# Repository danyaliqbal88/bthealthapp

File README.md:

# HealthApp
First app
"# bthealthapp" 
Ionic app for Riko chi.
The Riko Chi is an ultra low power, ultra light, ultra small wearable smartwatch. It monitors the ECG and the PPG 
signals to calculate your blood pressure non-invasively.The smartwatch must be calibrated
1. The physical address of the HC-05 Bluetooth module is hardcoded. Change it in index.js file according to your 
Hardware module.

Warning:
Despite the chic 3D printable design, the Riko Chi is a biomedical device and should be treated as a medical 
instrument for all intents and purposes. The Riko Chi must be re- calibrated for each individual patient.
The calibration process requires the patient to undergo a cardiac exercise test while wearing the Riko Chi in 
calibration mode and simultaneous reading obtained from an automatic cuff based blood pressure machine at 
regular intervals. Once the device has been calibrated, it can estimate the systolic Blood pressure of that individual 
with a mean error of +- 10.6 mmHG.
Beware:The risk for electric shock and accidental injury or loss of life exists.

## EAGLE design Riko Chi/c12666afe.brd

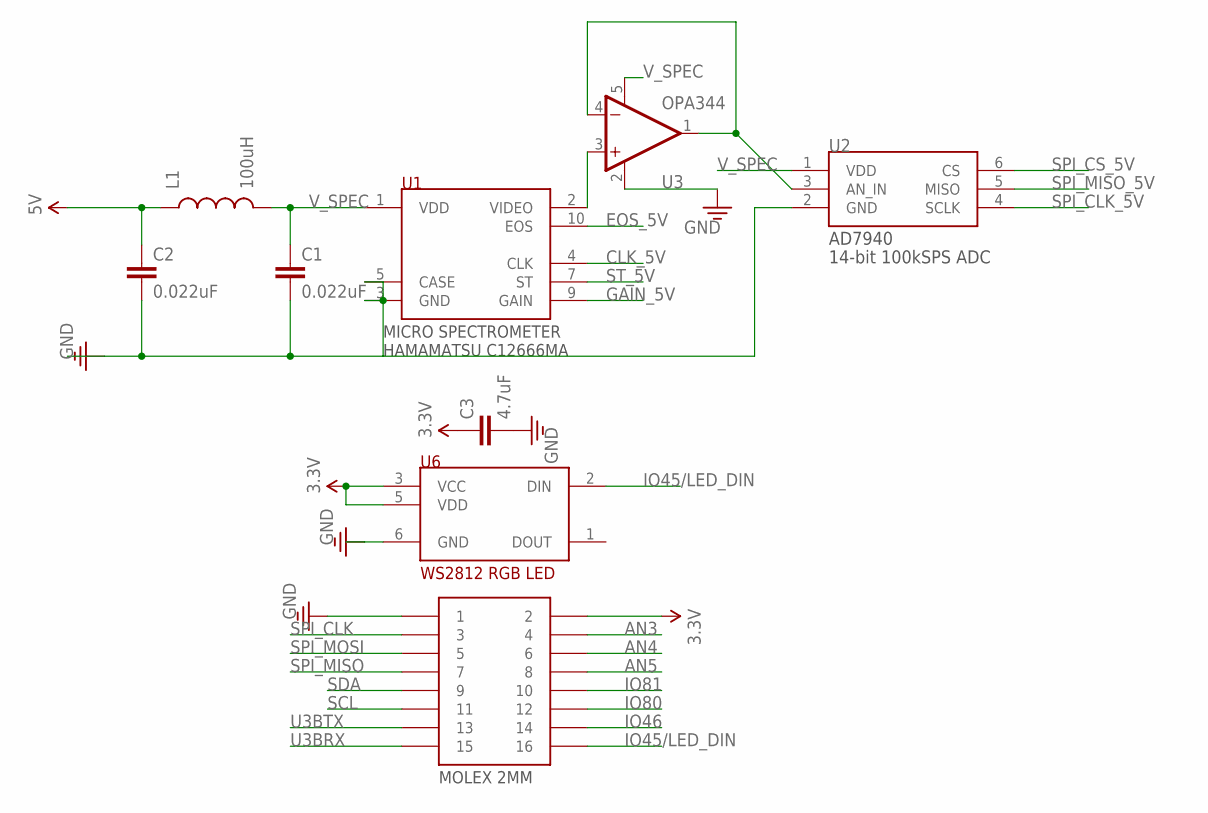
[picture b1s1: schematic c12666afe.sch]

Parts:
2MMCONNECTOR: CON-MOLEX-2MMMALE; MOLEX-0877591650
C1, C2: 0.022uF; 0603
C3: 4.7uF; 0603
L1: 100uH; 0805
U1: MICROSPEC-C12666MA; C12666MA
U2: AD7940; SOT-23-6L
U3: OPA344; SOT23-5
U6: WS2812_NEOPIXEL; WS2812

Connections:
3.3V: 2MMCONNECTOR.2, C3.1, U6.3 (VCC), U6.5 (VDD)
5V: C2.1, L1.1
AN3: 2MMCONNECTOR.4
AN4: 2MMCONNECTOR.6
AN5: 2MMCONNECTOR.8
CLK_5V: U1.4 (CLK)
EOS_5V: U1.10 (EOS)
GAIN_5V: U1.9 (GAIN)
GND: 2MMCONNECTOR.1, C1.2, C2.2, C3.2, U1.3 (GND), U1.5 (CASE), U2.2 (GND), U3.2 (V-), U6.6 (GND)
IO45/LED_DIN: 2MMCONNECTOR.16, U6.2 (DIN)
IO46: 2MMCONNECTOR.14
IO80: 2MMCONNECTOR.12
IO81: 2MMCONNECTOR.10
unnamed: U2.3 (AN_IN), U3.1 (OUT), U3.4 (-IN)
unnamed: U1.2 (VIDEO), U3.3 (+IN)
SCL: 2MMCONNECTOR.11
SDA: 2MMCONNECTOR.9
SPI_CLK: 2MMCONNECTOR.3
SPI_CLK_5V: U2.4 (SCLK)
SPI_CS_5V: U2.6 (CS)
SPI_MISO: 2MMCONNECTOR.7
SPI_MISO_5V: U2.5 (MISO)
SPI_MOSI: 2MMCONNECTOR.5
ST_5V: U1.7 (ST)
U3BRX: 2MMCONNECTOR.15
U3BTX: 2MMCONNECTOR.13
V_SPEC: C1.1, L1.2, U1.1 (VDD), U2.1 (VDD), U3.5 (V+)

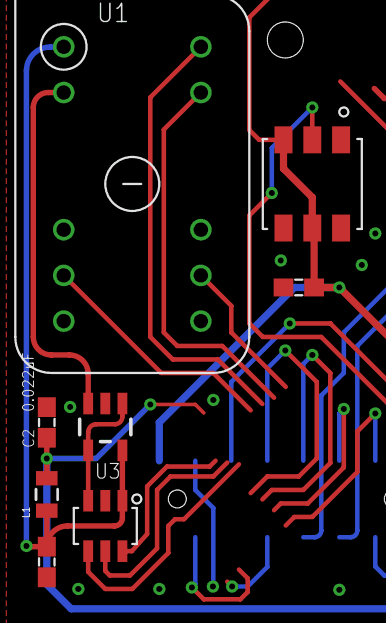
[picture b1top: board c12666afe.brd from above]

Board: 2 copper layers, 9 parts (1 on the bottom side), 7 nets.

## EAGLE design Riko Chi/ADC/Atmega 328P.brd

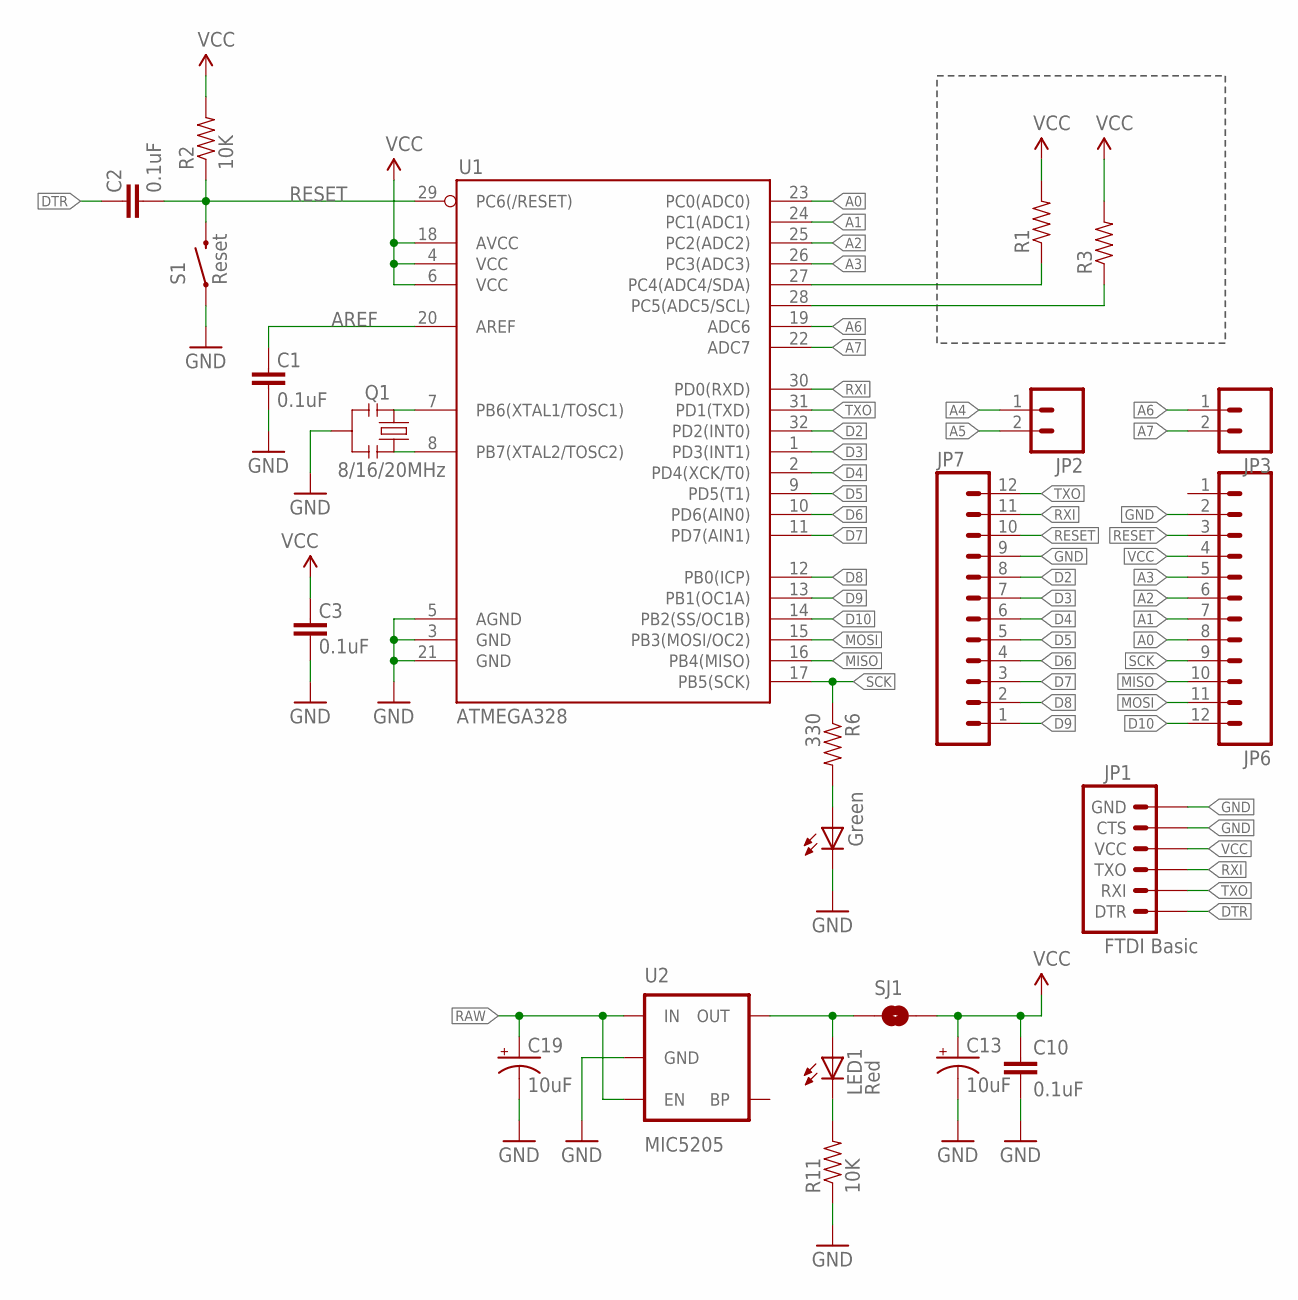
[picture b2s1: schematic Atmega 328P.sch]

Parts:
C1, C2, C3, C10: 0.1uF; 0603-CAP
C13, C19: 10uF; EIA3216
D3: Green; 0603-LED-ALT1
JP1: FTDI Basic; 1X06
JP2, JP3: M02PTH; 1X02
JP6, JP7: M12PTH; 1X12
LED1: Red; 0603-LED-ALT1
Q1: 8/16/20MHz; RESONATOR-SMD-1:1
R1, R3: RESISTOR0603-RES; 0603-RES
R2, R11: 10K; 0603-RES
R6: 330; 0603-RES
S1: Reset; TACTILE-SWITCH-SMD-ALT01
SJ1: SOLDERJUMPERNC; SJ_2S
U1: ATMEGA328; TQFP32-08
U2: MIC5205; SOT23-5

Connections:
A0: JP6.8, U1.23 (PC0(ADC0))
A1: JP6.7, U1.24 (PC1(ADC1))
A2: JP6.6, U1.25 (PC2(ADC2))
A3: JP6.5, U1.26 (PC3(ADC3))
A4: JP2.1, R1.1, U1.27 (PC4(ADC4/SDA))
A5: JP2.2, R3.1, U1.28 (PC5(ADC5/SCL))
A6: JP3.1, U1.19 (ADC6)
A7: JP3.2, U1.22 (ADC7)
AREF: C1.2, U1.20 (AREF)
D2: JP7.8, U1.32 (PD2(INT0))
D3: JP7.7, U1.1 (PD3(INT1))
D4: JP7.6, U1.2 (PD4(XCK/T0))
D5: JP7.5, U1.9 (PD5(T1))
D6: JP7.4, U1.10 (PD6(AIN0))
D7: JP7.3, U1.11 (PD7(AIN1))
D8: JP7.2, U1.12 (PB0(ICP))
D9: JP7.1, U1.13 (PB1(OC1A))
D10: JP6.12, U1.14 (PB2(SS/OC1B))
DTR: C2.2, JP1.1 (DTR)
GND: C1.1, C3.1, C10.2, C13.C (-), C19.C (-), D3.C, JP1.5 (CTS), JP1.6 (GND), JP6.2, JP7.9, Q1.2, R11.1, S1.1, S1.2 (1), U1.3 (GND), U1.5 (AGND), U1.21 (GND), U2.2 (GND)
MISO: JP6.10, U1.16 (PB4(MISO))
MOSI: JP6.11, U1.15 (PB3(MOSI/OC2))
unnamed: Q1.3, U1.8 (PB7(XTAL2/TOSC2))
unnamed: Q1.1, U1.7 (PB6(XTAL1/TOSC1))
unnamed: LED1.A, SJ1.1, U2.5 (OUT)
unnamed: LED1.C, R11.2
unnamed: D3.A, R6.2
RAW: C19.A (+), U2.1 (IN), U2.3 (EN)
RESET: C2.1, JP6.3, JP7.10, R2.1, S1.3 (2), S1.4 (2), U1.29 (PC6(/RESET))
RXI: JP1.3 (TXO), JP7.11, U1.30 (PD0(RXD))
SCK: JP6.9, R6.1, U1.17 (PB5(SCK))
TXO: JP1.2 (RXI), JP7.12, U1.31 (PD1(TXD))
VCC: C3.2, C10.1, C13.A (+), JP1.4 (VCC), JP6.4, R1.2, R2.2, R3.2, SJ1.2, U1.4 (VCC), U1.6 (VCC), U1.18 (AVCC)

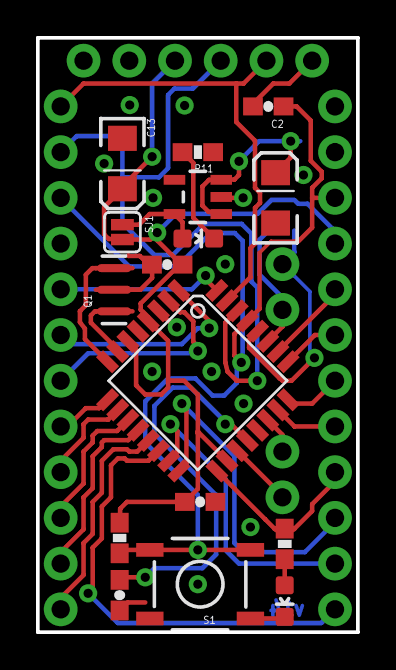
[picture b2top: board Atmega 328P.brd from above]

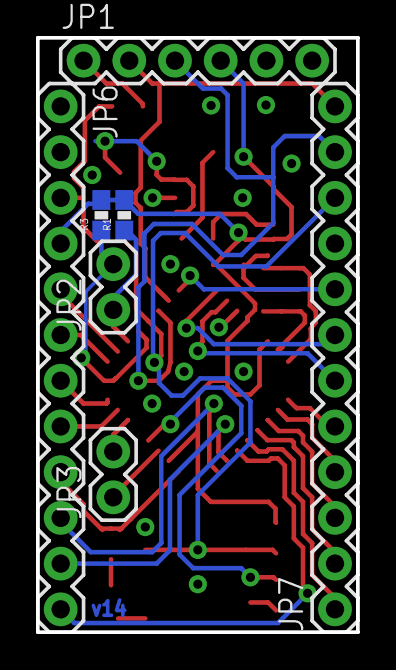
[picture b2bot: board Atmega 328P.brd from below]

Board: 2 copper layers, 17.8 x 33.0 mm, 23 parts (7 on the bottom side), 33 nets.

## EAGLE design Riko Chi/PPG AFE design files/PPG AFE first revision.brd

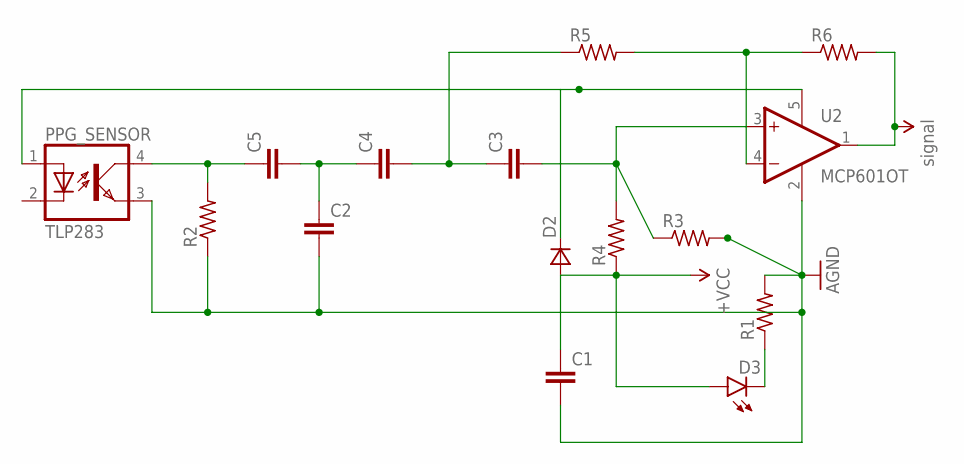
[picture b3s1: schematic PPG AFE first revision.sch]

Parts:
C1, C2, C3, C4, C5: CC0201; C0201
D2: DSOD323; SOD323
D3: LED-FKIT-1206; FKIT-LED-1206
PPG_SENSOR: TLP283; MINI-FLAT-4
R1, R2, R3, R4, R5, R6: R-US_R0603; R0603
U2: MCP601OT; SOT23-5

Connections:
AGND: C1.2, C2.2, PPG_SENSOR.3 (EMIT), R1.2, R2.1, R3.2, U2.2 (V-)
unnamed: C3.2, R3.1, R4.2, U2.3 (+IN)
unnamed: R5.2, R6.1, U2.4 (-IN)
unnamed: D2.1 (C), PPG_SENSOR.1 (A), U2.5 (V+)
unnamed: C3.1, C4.2, R5.1
unnamed: C2.1, C4.1, C5.2
unnamed: C5.1, PPG_SENSOR.4 (COL), R2.2
unnamed: D3.C, R1.1
VCC: C1.1, D2.2 (A), D3.A, R4.1
VCC_1: R6.2, U2.1 (OUT)

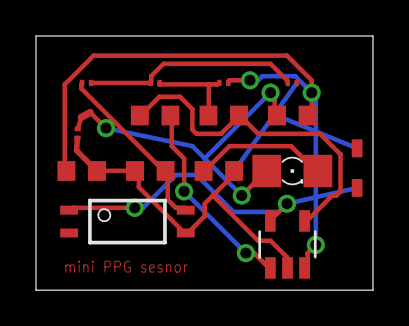
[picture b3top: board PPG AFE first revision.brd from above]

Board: 2 copper layers, 18.7 x 14.1 mm, 15 parts (0 on the bottom side), 10 nets.

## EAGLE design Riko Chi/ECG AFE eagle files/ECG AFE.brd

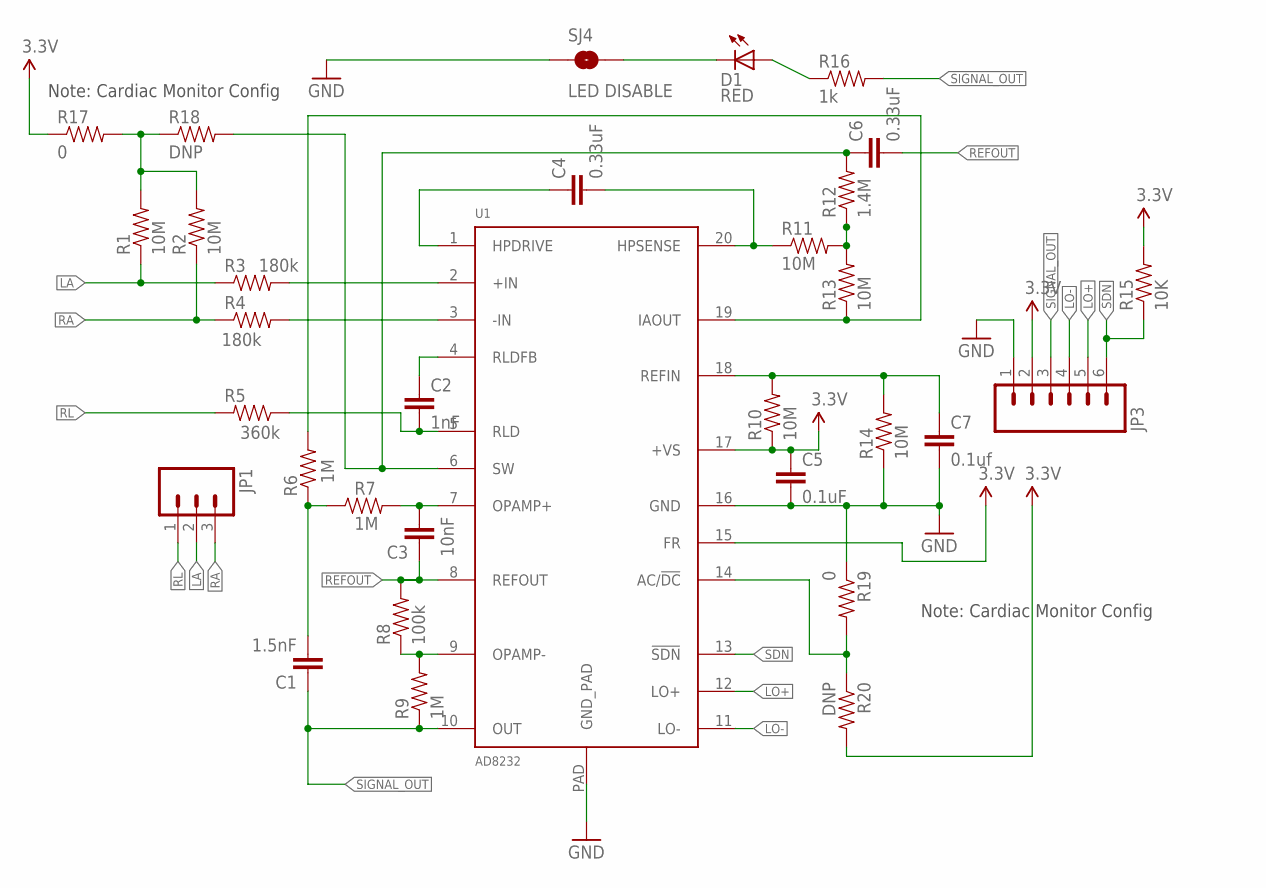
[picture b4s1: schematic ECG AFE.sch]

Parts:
C1: 1.5nF; 0603-CAP
C2: 1nF; 0603-CAP
C3: 10nF; 0603-CAP
C4, C6: 0.33uF; 0805
C5: 0.1uF; 0603-CAP
C7: 0.1uf; 0603-CAP
D1: RED; LED-0603
JP1: M03PTH; 1X03
JP3: M06SIP; 1X06
R1, R2, R10, R11, R13, R14: 10M; 0603-RES
R3, R4: 180k; 0603-RES
R5: 360k; 0603-RES
R6, R7, R9: 1M; 0603-RES
R8: 100k; 0603-RES
R12: 1.4M; 0603-RES
R15: 10K; 0603-RES
R16: 1k; 0603-RES
R17, R19: 0; 0603
R18, R20: DNP; 0603
SJ4: LED DISABLE; SJ_2S-TRACE
U1: AD8232; LFCSP_20

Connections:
3.3V: C5.1, JP3.2, R10.1, R15.2, R17.1, R20.2, U1.15 (FR), U1.17 (+VS)
GND: C5.2, C7.2, JP3.1, R14.1, R19.1, SJ4.1, U1.16 (GND), U1.PAD (GND_PAD)
LA: JP1.2, R1.1, R3.1
LO+: JP3.5, U1.12 (LO+)
LO-: JP3.4, U1.11 (LO-)
unnamed: R3.2, U1.2 (+IN)
unnamed: R4.2, U1.3 (-IN)
unnamed: C3.2, R7.2, U1.7 (OPAMP+)
unnamed: C4.2, R11.1, U1.20 (HPSENSE)
unnamed: C7.1, R10.2, R14.2, U1.18 (REFIN)
unnamed: D1.A, R16.1
unnamed: R8.1, R9.2, U1.9 (OPAMP-)
unnamed: R6.2, R13.1, U1.19 (IAOUT)
unnamed: C1.2, R6.1, R7.1
unnamed: D1.C, SJ4.2
unnamed: R19.2, R20.1, U1.14 (AC/!DC)
unnamed: C4.1, U1.1 (HPDRIVE)
unnamed: R11.2, R12.1, R13.2
unnamed: C6.1, R12.2, R18.2, U1.6 (SW)
unnamed: C2.1, U1.4 (RLDFB)
unnamed: C2.2, R5.1, U1.5 (RLD)
unnamed: R1.2, R2.2, R17.2, R18.1
RA: JP1.3, R2.1, R4.1
REFOUT: C3.1, C6.2, R8.2, U1.8 (REFOUT)
RL: JP1.1, R5.2
SDN: JP3.6, R15.1, U1.13 (!SDN)
SIGNAL_OUT: C1.1, JP3.3, R9.1, R16.2, U1.10 (OUT)

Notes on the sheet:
Note: Cardiac Monitor Config

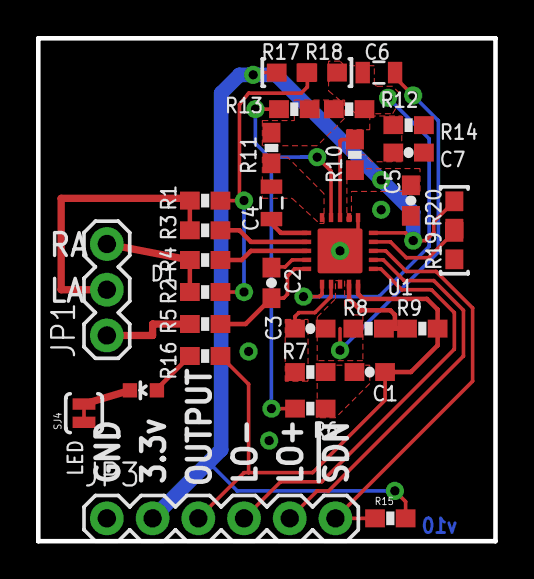
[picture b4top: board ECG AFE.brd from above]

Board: 2 copper layers, 25.4 x 27.9 mm, 32 parts (0 on the bottom side), 27 nets.

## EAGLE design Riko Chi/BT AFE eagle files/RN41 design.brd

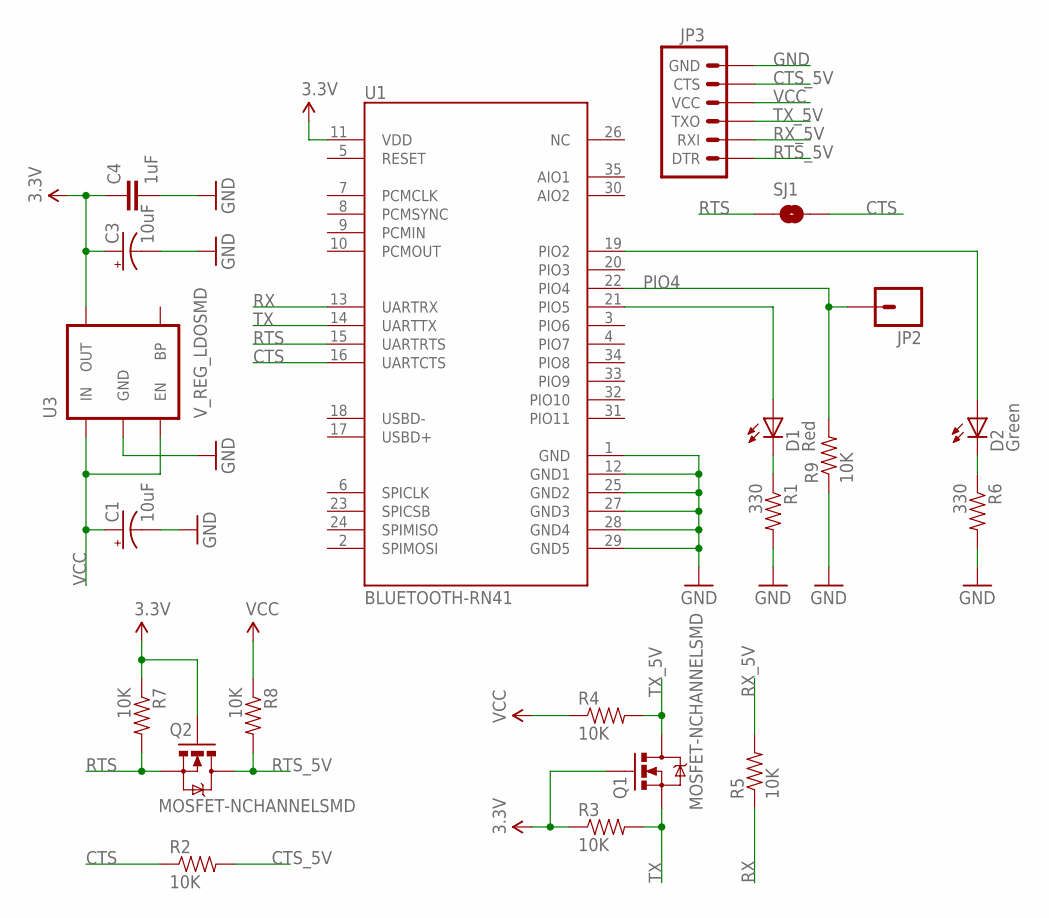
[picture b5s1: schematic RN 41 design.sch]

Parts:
C1, C3: 10uF; EIA3216
C4: 1uF; 0402-CAP
D1: Red; LED-0603
D2: Green; LED-0603
JP2: M01SMDNS; 1X01NS
JP3: ARDUINO_SERIAL_PROGRAMPTH; 1X06
Q1, Q2: MOSFET-NCHANNELSMD; SOT23-3
R1, R6: 330; 0402-RES
R2, R3, R4, R5, R7, R8, R9: 10K; 0402-RES
SJ1: SOLDERJUMPERNO; SJ_2S-NO
U1: BLUETOOTH-RN41; RN41
U3: V_REG_LDOSMD; SOT23-5

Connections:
3.3V: C3.A (+), C4.1, Q1.1 (G), Q2.1 (G), R3.1, R7.1, U1.11 (VDD), U3.5 (OUT)
CTS: R2.1, SJ1.2, U1.16 (UARTCTS)
CTS_5V: JP3.5 (CTS), R2.2
D1: D1.C, R1.1
D2: D2.C, R6.1
GND: C1.C (-), C3.C (-), C4.2, JP3.6 (GND), R1.2, R6.2, R9.1, U1.1 (GND), U1.12 (GND1), U1.25 (GND2), U1.27 (GND3), U1.28 (GND4), U1.29 (GND5), U3.2 (GND)
unnamed: D1.A, U1.21 (PIO5)
unnamed: D2.A, U1.19 (PIO2)
PIO4: JP2.1, R9.2, U1.22 (PIO4)
RTS: Q2.2 (S), R7.2, SJ1.1, U1.15 (UARTRTS)
RTS_5V: JP3.1 (DTR), Q2.3 (D), R8.2
RX: R5.1, U1.13 (UARTRX)
RX_5V: JP3.2 (RXI), R5.2
TX: Q1.2 (S), R3.2, U1.14 (UARTTX)
TX_5V: JP3.3 (TXO), Q1.3 (D), R4.2
VCC: C1.A (+), JP3.4 (VCC), R4.1, R8.1, U3.1 (IN), U3.3 (EN)

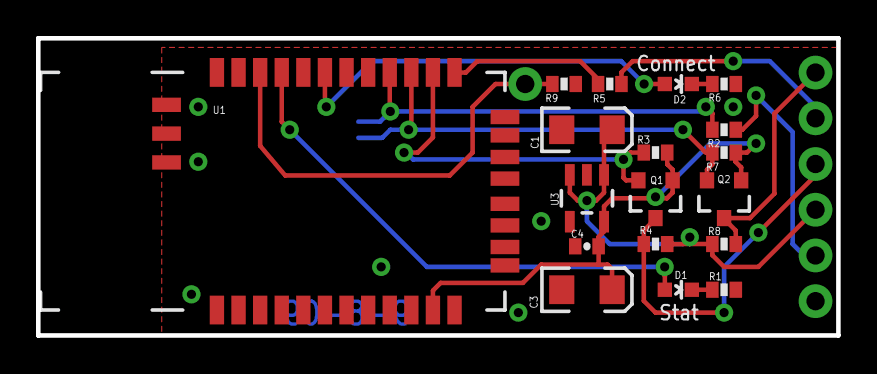
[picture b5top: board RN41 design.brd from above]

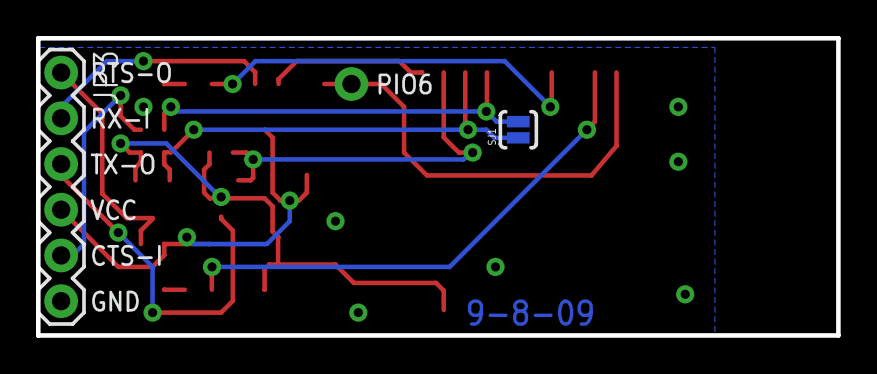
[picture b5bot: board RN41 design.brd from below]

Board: 2 copper layers, 44.5 x 16.5 mm, 21 parts (2 on the bottom side), 16 nets.

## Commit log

2016-09-16 second commit
2016-10-11 added working ECG,PPG design files
2016-10-11 added source for analog read from AFE
2016-10-12 signal processing files and raw data
2016-10-12 added more data, more results, more stats, more plots
2016-10-12 added description
2016-10-12 line graphs added
2016-10-12 Ionic app
2016-10-12 added readme
2016-10-12 communications blocks
2016-10-12 modified Riko chi 3d design
2016-10-12 modified Riko Chi stl file
2016-10-20 added screenshots
2016-12-09 c12666ma analog front end files added
2016-12-18 draft added

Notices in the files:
parts and their libraries:
SparkFun-Passives: Licensing: CC v3.0 Share-Alike You are welcome to use this library for commercial purposes.
SparkFun-LED: Licensing: Creative Commons ShareAlike 4.0 International - https://creativecommons.org/licenses/by-sa/4.0
